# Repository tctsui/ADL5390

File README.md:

# ADL5390
This is a PCB design for an RF vector multiplier ADL5390 from Analog Devices. The functionality and design of this board is similar to the original evaluation board design. The purpose of this board is to solve the problem of crosstalk between the I-channel and the Q-channel in the original evaluation board. The main modification is the use of differential inputs on the two-channels with  a 180 hybrid coupler SYPJ-2-33+.

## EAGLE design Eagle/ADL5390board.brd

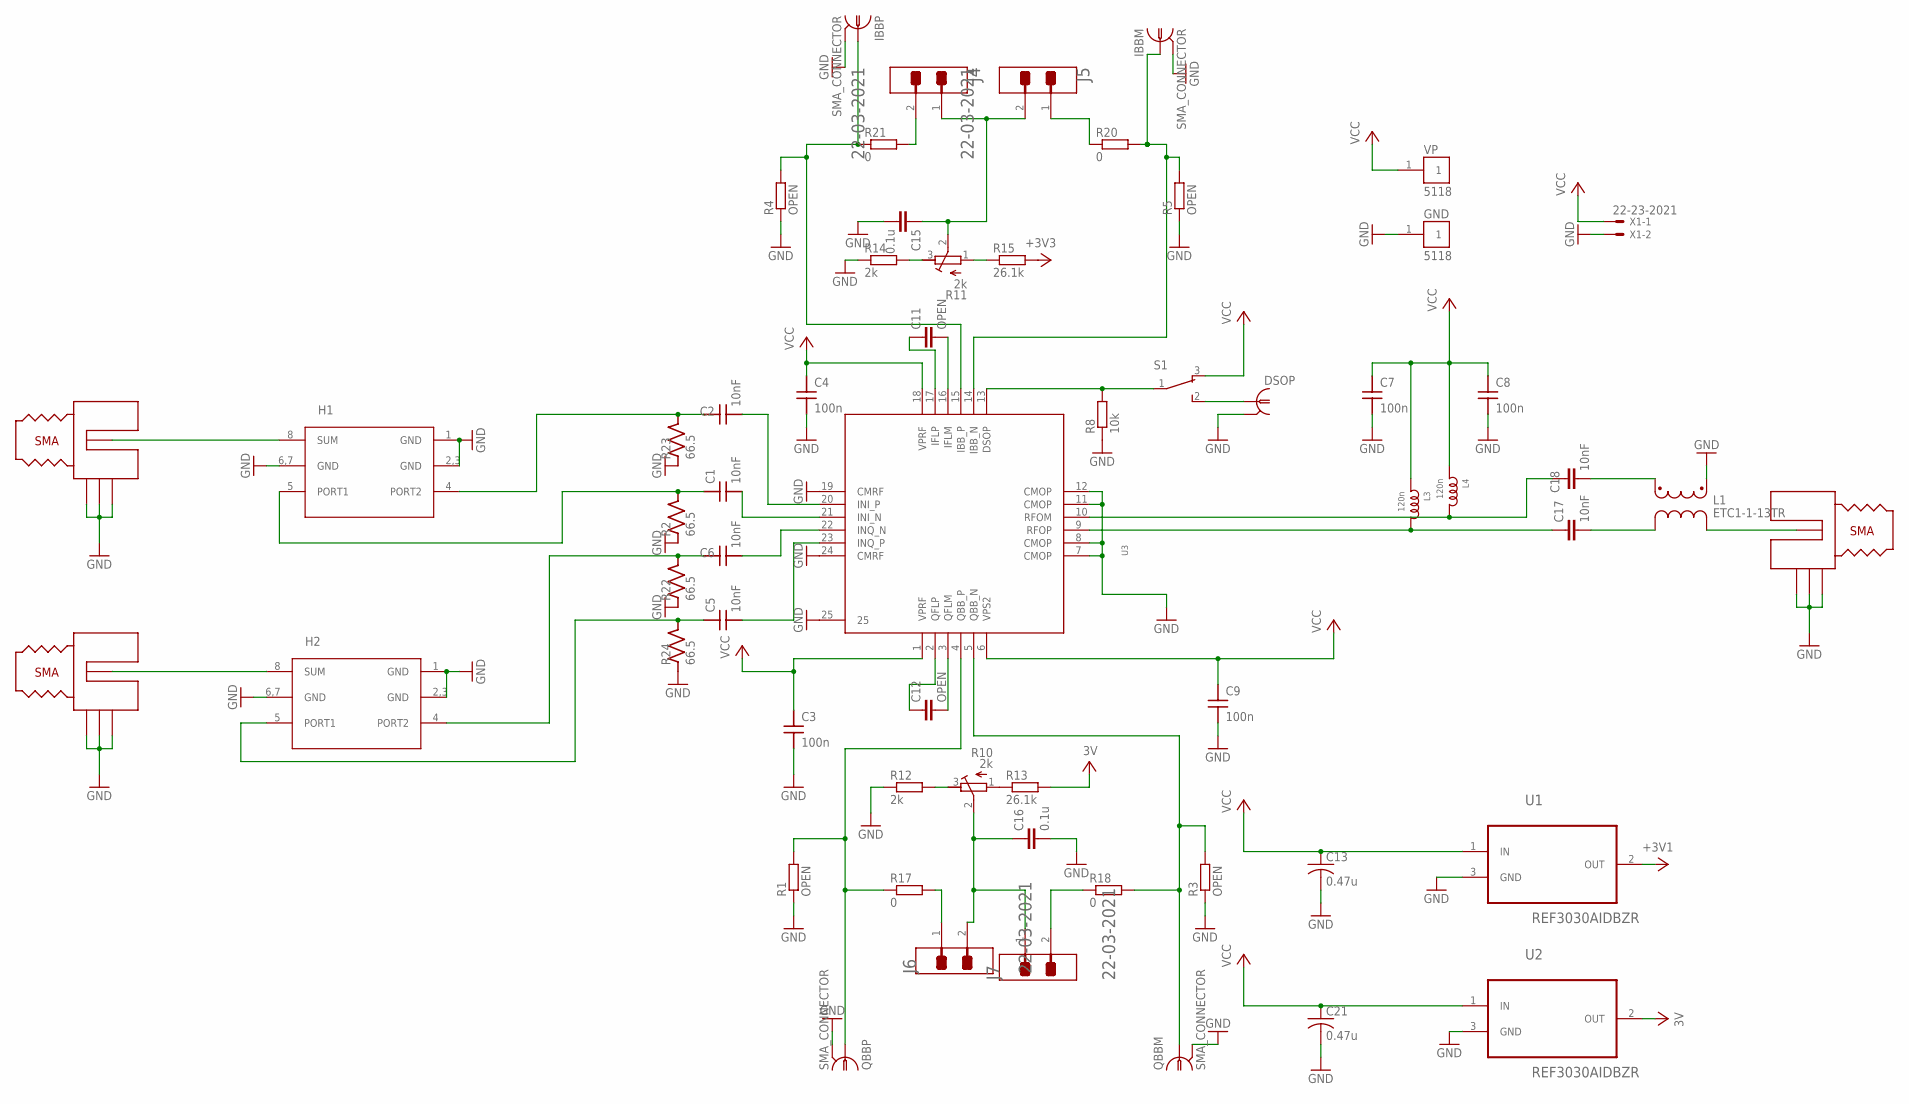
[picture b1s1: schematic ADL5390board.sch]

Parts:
C1, C2, C5, C6: 10nF; C_MLCC_0402; PARTNO C1005C0G1H102J050BA; DIGIKEY 445-6846-1-ND
C3, C4, C7, C8, C9: 100n; C_MLCC_0204; PARTNO EWK105C6104MPHF; DIGIKEY 587-5138-1-ND
C11, C12: OPEN; C0603
C13, C21: 0.47u; C0603; PARTNO CL10B474KA8NFNC; DIGIKEY 1276-2082-1-ND
C15, C16: 0.1u; C0603; PARTNO CL10B104KA8NNNC; DIGIKEY 1276-1006-1-ND
C17, C18: 10nF; C0402; PARTNO C1005C0G1H102J050BA; DIGIKEY 445-6846-1-ND
DSOP: SMA_CONNECTOR; QKDLAB_JOSH_MECHANICAL_JOHNSON_SMA_EDGE_LAUNCH_142-0701-851
GND: 5118; TP_5118; PARTNO 5118; DIGIKEY 36-5118-ND
H1, H2: SYPJ-2-33+; PL-274
IBBM: SMA_CONNECTOR; QKDLAB_JOSH_MECHANICAL_JOHNSON_SMA_EDGE_LAUNCH_142-0701-851; DIGIKEY J658-ND
IBBP: SMA_CONNECTOR; QKDLAB_JOSH_MECHANICAL_JOHNSON_SMA_EDGE_LAUNCH_142-0701-851; DIGIKEY J658-ND
J1, J2, J3: QKDLAB_JOSH_MECHANICAL_JOHNSON_SMA_18GHZ_142-0761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; QKDLAB_JOSH_MECHANICAL_JOHNSON_SMA_18GHZ_4-LAYER_142-0761-8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; PARTNO 901-10511-2; DIGIKEY ARF2499-ND
J4, J5, J6, J7: MOLEX_22-03-2021MOLEX_22-03-2021_0_0; MOLEX_22-03-2021_0
L1: ETC1-1-13TR; SM22; DIGIKEY 1465-1217-1-ND
L3, L4: 120n; R0603; PARTNO LQW18ASR12G0CD; DIGIKEY 490-LQW18ASR12G0CDCT-ND
QBBM: SMA_CONNECTOR; QKDLAB_JOSH_MECHANICAL_JOHNSON_SMA_EDGE_LAUNCH_142-0701-851; DIGIKEY J658-ND
QBBP: SMA_CONNECTOR; QKDLAB_JOSH_MECHANICAL_JOHNSON_SMA_EDGE_LAUNCH_142-0701-851; DIGIKEY J658-ND
R1, R3, R4, R5: OPEN; R0603; PARTNO CRCW06030000Z0EA; DIGIKEY 541-0.0GCT-ND
R2, R22, R23, R24: 66.5; R_0402; PARTNO ERJ-2RKF66R5X; DIGIKEY P66.5LDKR-ND
R8: 10k; R0603; PARTNO ERA-3AEB103V; DIGIKEY P10KDBCT-ND
R10, R11: 2k; RTRIM3296W; PARTNO PV36W202C01B00; DIGIKEY 490-2880-ND
R12, R14: 2k; R0603; PARTNO ERA-3AEB202V; DIGIKEY P2.0KDBCT-ND
R13, R15: 26.1k; R0603; PARTNO ERA-3AEB2612V; DIGIKEY P26.1KDBCT-ND
R17, R18, R20, R21: 0; R0603; PARTNO CRCW06030000Z0EA; DIGIKEY 541-0.0GCT-ND
S1: 450301014042; DIGIKEY 450301014042-ND
U1, U2: REF3030AIDBZR; SOT95P237X112-3N
U3: ADL5390_ADL5390; PARTNO ADL5390ACPZ-REEL7; DIGIKEY ADL5390ACPZ-REEL7CT-ND
VP: 5118; TP_5118; PARTNO 5000; DIGIKEY 36-5000-ND
X1: 22-23-2021

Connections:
+3V3: R15.2, U1.2 (OUT)
DSOP: R8.2, S1.1, U3.13 (DSOP)
GND: C3.P$2 (2), C4.P$2 (2), C7.P$2 (2), C8.P$2 (2), C9.P$2 (2), C13.2, C15.2, C16.2, C21.2, DSOP.P$2 (2), DSOP.P$3 (2), DSOP.P$4 (2), DSOP.P$5 (2), GND.1, H1.1 (GND), H1.2,3 (GND), H1.6,7 (GND), H2.1 (GND), H2.2,3 (GND), H2.6,7 (GND), IBBM.P$2 (2), IBBM.P$3 (2), IBBM.P$4 (2), IBBM.P$5 (2), IBBP.P$2 (2), IBBP.P$3 (2), IBBP.P$4 (2), IBBP.P$5 (2), J1.P$2 (GND), J1.P$3 (GND), J1.P$4 (GND), J2.P$2 (GND), J2.P$3 (GND), J2.P$4 (GND), J3.P$2 (GND), J3.P$3 (GND), J3.P$4 (GND), L1.1, QBBM.P$2 (2), QBBM.P$3 (2), QBBM.P$4 (2), QBBM.P$5 (2), QBBP.P$2 (2), QBBP.P$3 (2), QBBP.P$4 (2), QBBP.P$5 (2), R1.1, R2.P$1 (1), R3.1, R4.1, R5.1, R8.1, R12.1, R14.1, R22.P$1 (1), R23.P$1 (1), R24.P$1 (1), U1.3 (GND), U2.3 (GND), U3.7 (CMOP), U3.8 (CMOP), U3.11 (CMOP), U3.12 (CMOP), U3.19 (CMRF), U3.24 (CMRF), U3.25, X1.2
IBB_N: IBBM.P$1 (1), R5.2, R20.2, U3.14 (IBB_N)
IBB_P: IBBP.P$1 (1), R4.2, R21.1, U3.15 (IBB_P)
IFL_N: C11.2, U3.16 (IFLM)
IFL_P: C11.1, U3.17 (IFLP)
INI_N: C1.P$2 (2), U3.21 (INI_N)
INI_P: C2.P$2 (2), U3.20 (INI_P)
INQ_N: C6.P$2 (2), U3.22 (INQ_N)
INQ_P: C5.P$2 (2), U3.23 (INQ_P)
IN_N: H2.8 (SUM), J2.P$1 (SIG)
IN_P: H1.8 (SUM), J1.P$1 (SIG)
unnamed: R11.1 (A), R15.1
unnamed: R11.3 (E), R14.2
unnamed: C15.1, J4.1, J5.2, R11.2 (S)
unnamed: J4.2, R21.2
unnamed: J5.1, R20.1
unnamed: J6.1, R17.2
unnamed: J7.2, R18.1
unnamed: C16.1, J6.2, J7.1, R10.2 (S)
unnamed: R10.3 (E), R12.2
unnamed: R10.1 (A), R13.1
unnamed: C18.2, L1.5
unnamed: C17.2, L1.4
unnamed: J3.P$1 (SIG), L1.3
unnamed: DSOP.P$1 (1), S1.2
QBB_N: QBBM.P$1 (1), R3.2, R18.2, U3.5 (QBB_N)
QBB_P: QBBP.P$1 (1), R1.2, R17.1, U3.4 (QBB_P)
QFL_N: C12.2, U3.3 (QFLM)
QFL_P: C12.1, U3.2 (QFLP)
RFINI_N: C1.P$1 (1), H1.5 (PORT1), R2.P$2 (2)
RFINI_P: C2.P$1 (1), H1.4 (PORT2), R23.P$2 (2)
RFINQ_N: C6.P$1 (1), H2.4 (PORT2), R22.P$2 (2)
RFINQ_P: C5.P$1 (1), H2.5 (PORT1), R24.P$2 (2)
RFO_N: C18.1, L4.2, U3.10 (RFOM)
RFO_P: C17.1, L3.2, U3.9 (RFOP)
V+: R13.2, U2.2 (OUT)
VCC: C3.P$1 (1), C4.P$1 (1), C7.P$1 (1), C8.P$1 (1), C9.P$1 (1), C13.1, C21.1, L3.1, L4.1, S1.3, U1.1 (IN), U2.1 (IN), U3.1 (VPRF), U3.6 (VPS2), U3.18 (VPRF), VP.1, X1.1

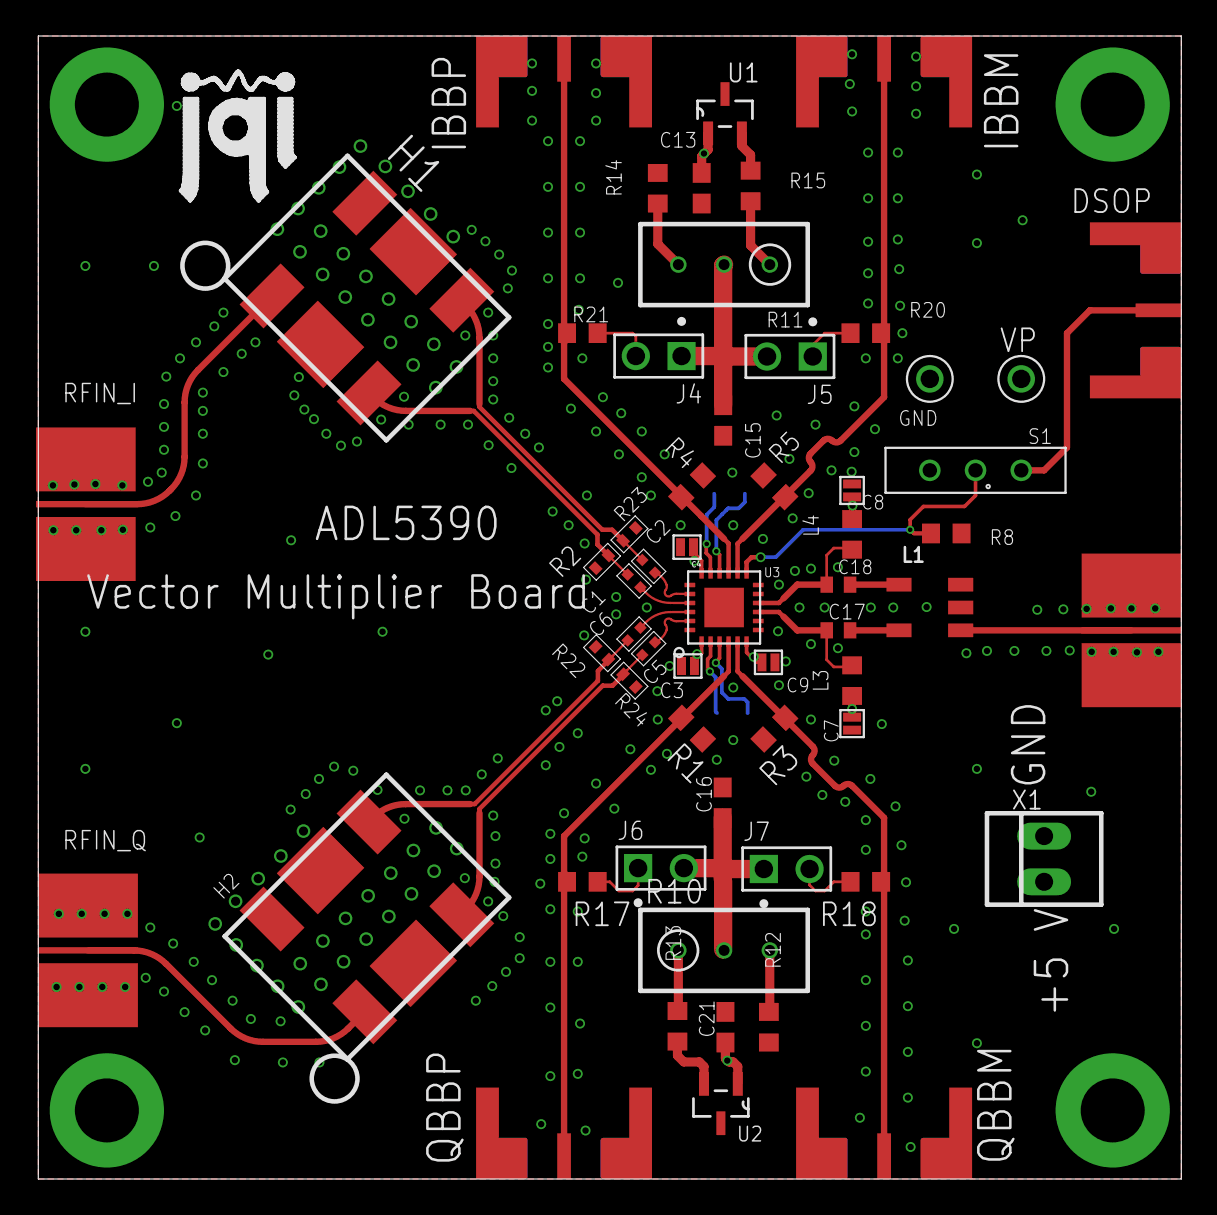
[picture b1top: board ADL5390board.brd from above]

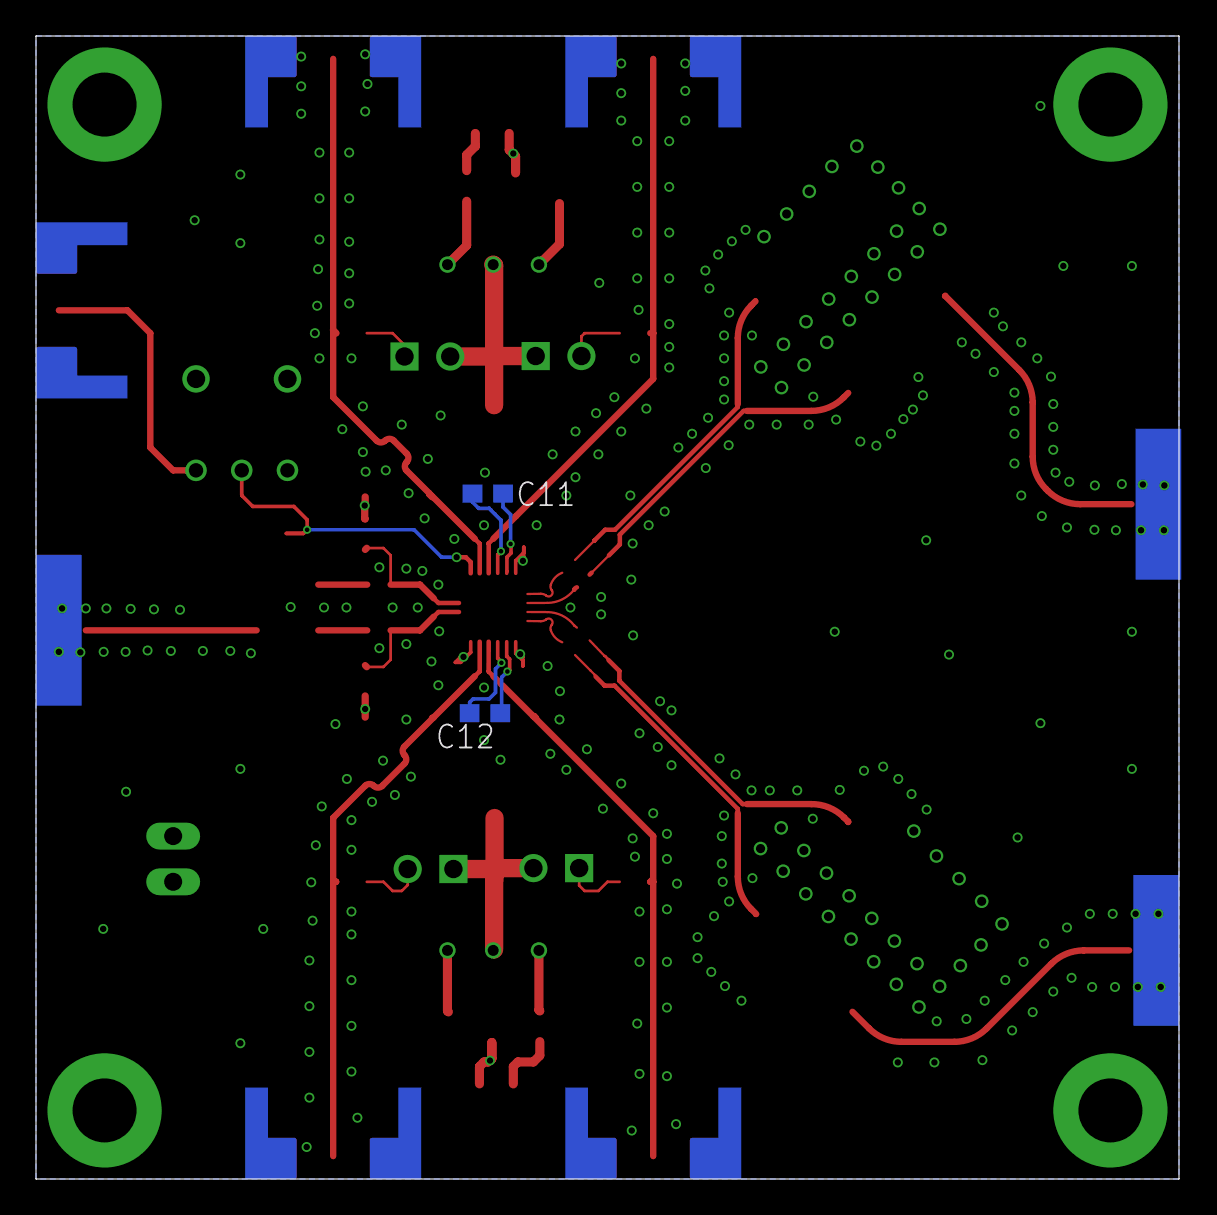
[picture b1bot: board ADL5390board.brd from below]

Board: 4 copper layers, 63.5 x 63.5 mm, 61 parts (2 on the bottom side), 39 nets.

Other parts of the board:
U$4: JQI_LOGO_POSITIVE-SILKSCREEN
